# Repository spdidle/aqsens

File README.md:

# aqsense

a pcb with air quality sensor...?

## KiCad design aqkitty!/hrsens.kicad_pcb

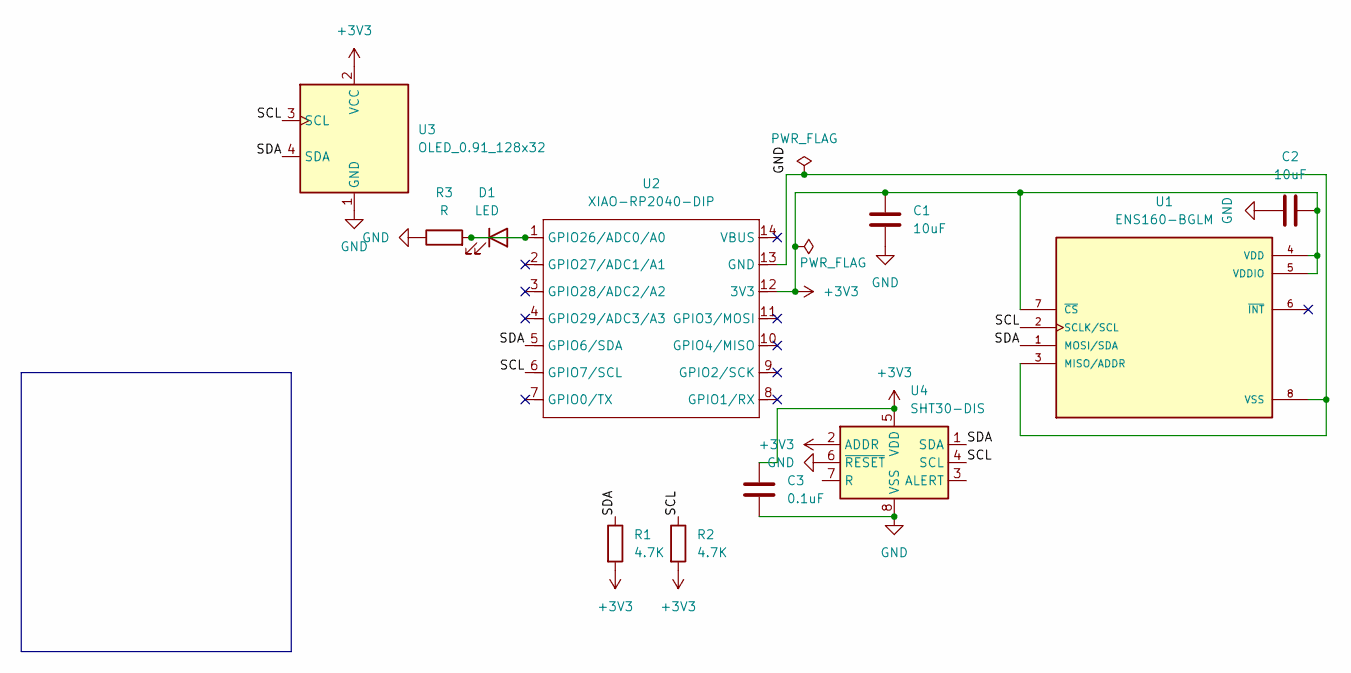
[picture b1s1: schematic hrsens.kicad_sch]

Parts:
C1, C2: 10uF; C_0603_1608Metric_Pad1.08x0.95mm_HandSolder
C3: 0.1uF; C_0603_1608Metric_Pad1.08x0.95mm_HandSolder
D1: LED; LED_0603_1608Metric_Pad1.05x0.95mm_HandSolder
R1, R2: 4.7K; R_Axial_DIN0207_L6.3mm_D2.5mm_P10.16mm_Horizontal
R3: R; R_0603_1608Metric_Pad0.98x0.95mm_HandSolder
U1: ENS160-BGLM; XDCR_ENS160-BGLM; PARTREV 1.3
U2: XIAO-RP2040-DIP
U3: OLED_0.91_128x32
U4: SHT30-DIS; Sensirion_DFN-8-1EP_2.5x2.5mm_P0.5mm_EP1.1x1.7mm

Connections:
+3V3: C1.1, C2.1, C3.1, R1.2, R2.2, U1.4 (VDD), U1.5 (VDDIO), U1.7 (~CS), U2.12 (3V3), U3.2 (VCC), U4.2 (ADDR), U4.5 (VDD)
/SCL: R2.1, U1.2 (SCLK/SCL), U2.6 (GPIO7/SCL), U3.3 (SCL), U4.4 (SCL)
/SDA: R1.1, U1.1 (MOSI/SDA), U2.5 (GPIO6/SDA), U3.4 (SDA), U4.1 (SDA)
GND: C1.2, C2.2, C3.2, R3.1, U1.3 (MISO/ADDR), U1.8 (VSS), U1.9 (VSS), U2.13 (GND), U3.1 (GND), U4.6 (~RESET), U4.8 (VSS), U4.9 (VSS)
unnamed: D1.1 (K), D1.2 (A), R3.2, U2.1 (GPIO26/ADC0/A0)

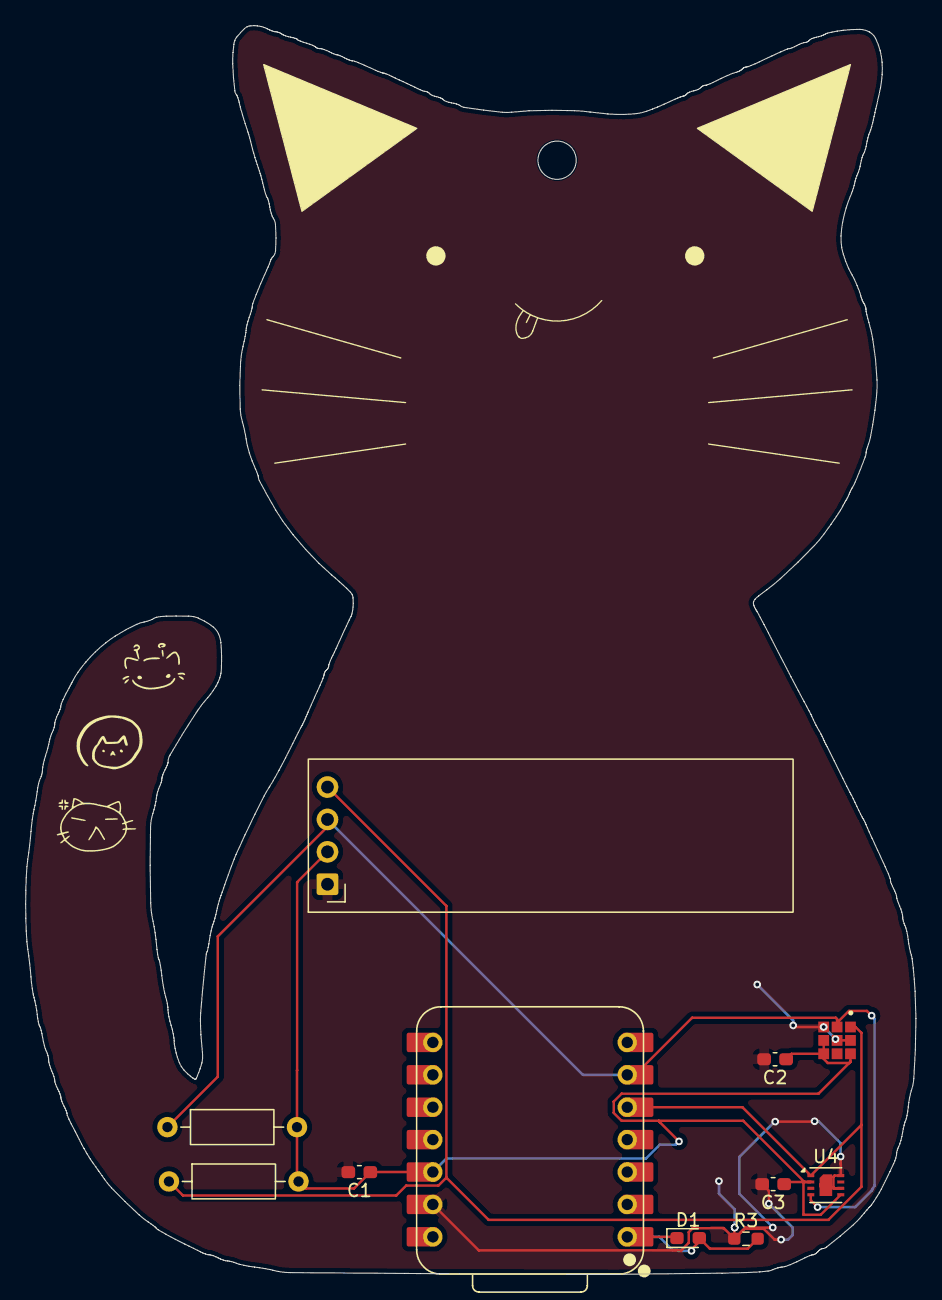
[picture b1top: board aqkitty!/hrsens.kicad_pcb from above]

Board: 2 copper layers, 69.8 x 97.9 mm, 11 parts (0 on the bottom side), 5 nets.

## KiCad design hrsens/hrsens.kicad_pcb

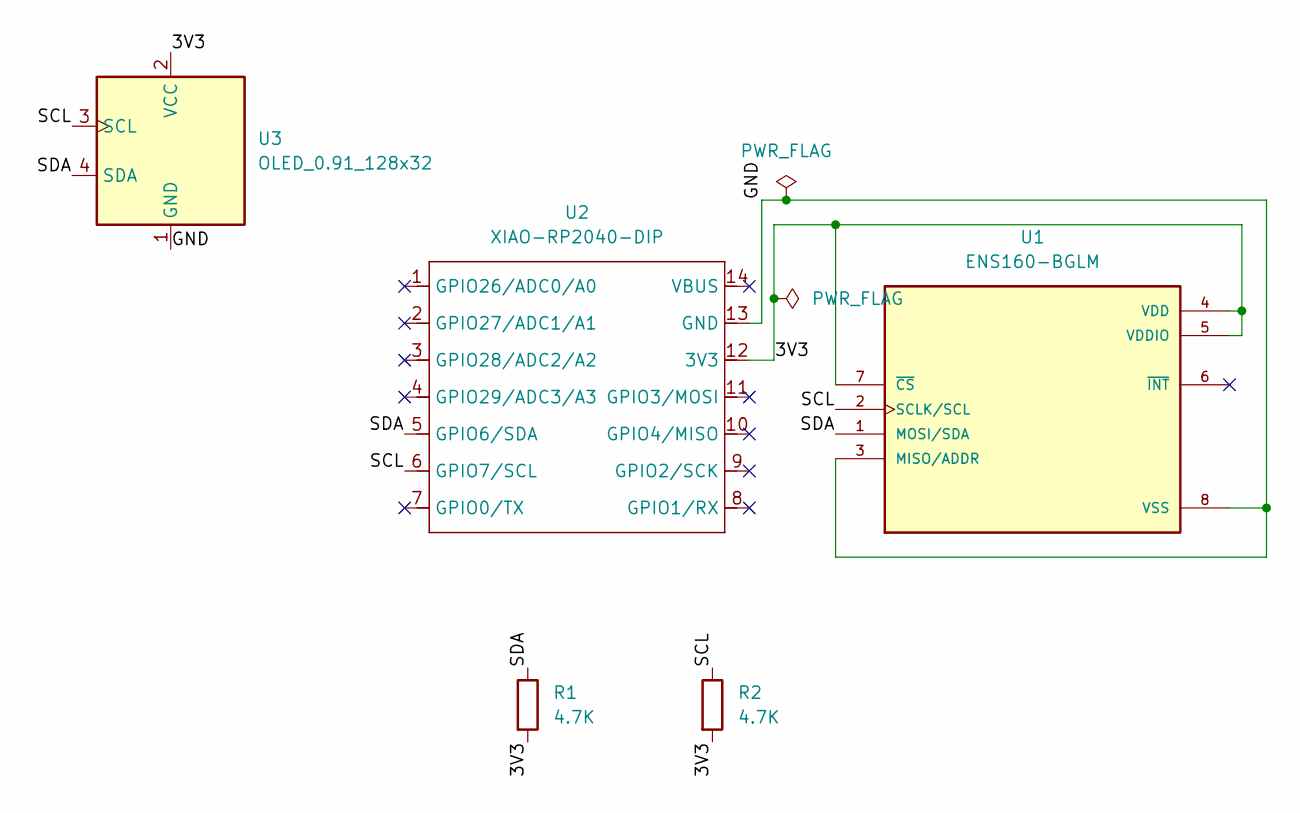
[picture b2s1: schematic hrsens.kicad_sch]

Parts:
R1, R2: 4.7K; R_Axial_DIN0207_L6.3mm_D2.5mm_P10.16mm_Horizontal
U1: ENS160-BGLM; XDCR_ENS160-BGLM; PARTREV 1.3
U2: XIAO-RP2040-DIP
U3: OLED_0.91_128x32

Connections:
/3V3: R1.2, R2.2, U1.4 (VDD), U1.5 (VDDIO), U1.7 (~CS), U2.12 (3V3), U3.2 (VCC)
/SCL: R2.1, U1.2 (SCLK/SCL), U2.6 (GPIO7/SCL), U3.3 (SCL)
/SDA: R1.1, U1.1 (MOSI/SDA), U2.5 (GPIO6/SDA), U3.4 (SDA)
VSS: U1.3 (MISO/ADDR), U1.8 (VSS), U1.9 (VSS), U2.13 (GND), U3.1 (GND)

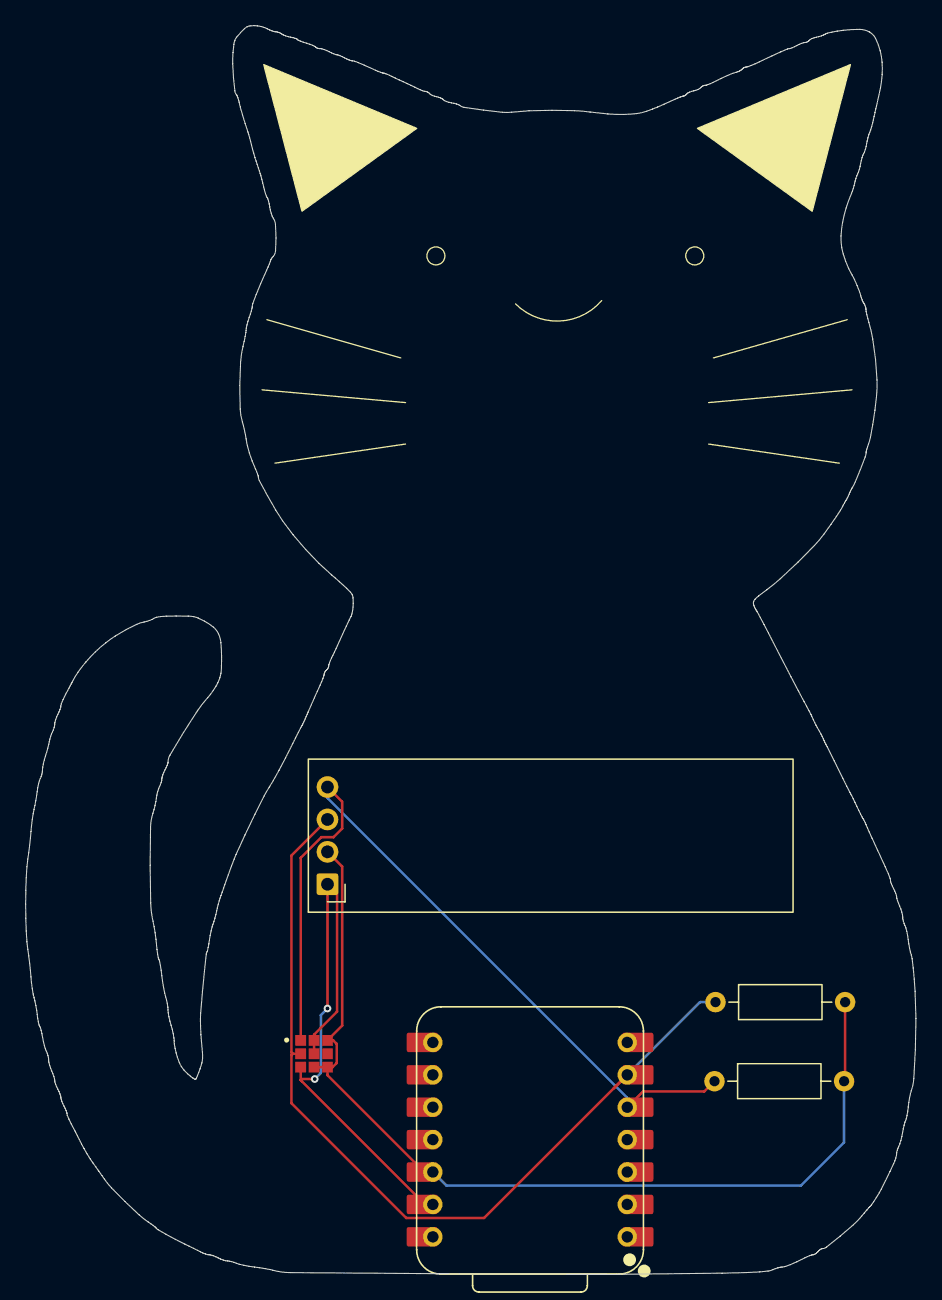
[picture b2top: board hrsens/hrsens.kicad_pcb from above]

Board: 2 copper layers, 69.8 x 97.9 mm, 5 parts (0 on the bottom side), 4 nets.

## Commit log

2026-04-06 start work
    start work! next sesh when i go home and gonna start tracing pcb
2026-04-07 update readme
    gulp. i was originally gonna do hr sensor but i gave up
2026-04-07 work
    this is the actual work bit that i did during the hackdash + a little at home. i finished doing copper traces buttt im not suree about where to go from hjere
2026-04-07 done tracing
    FR this time. some guy on slack told me my routing was inefficient so i lwk had to move everything ...! now i wait for parts iggg...?
2026-04-19 umm extra files
    i think they got left behind idk. check last commit
